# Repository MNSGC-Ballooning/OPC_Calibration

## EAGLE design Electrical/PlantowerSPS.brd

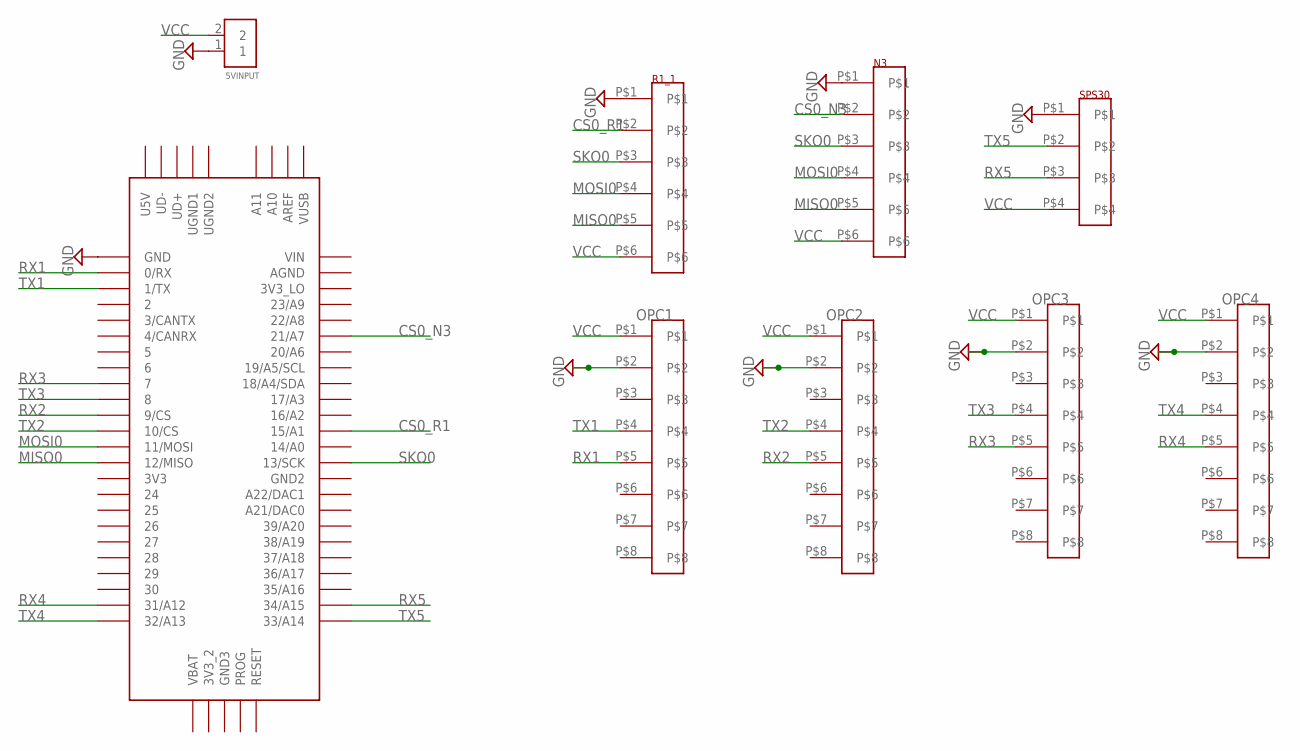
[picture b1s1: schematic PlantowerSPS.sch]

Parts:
5VINPUT: 2PIN_TERMINAL_BLOCK
N3: 6PINHEADER
OPC1, OPC2, OPC3, OPC4: 8PINHEADER
R1_1: 6PINHEADER
SPS30: 4PINHEADER
U$1: TEENSY_3.5/3.6

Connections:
CS0_N3: N3.P$2, U$1.21/A7
CS0_R1: R1_1.P$2, U$1.15/A1
GND: 5VINPUT.1, N3.P$1, OPC1.P$2, OPC2.P$2, OPC3.P$2, OPC4.P$2, R1_1.P$1, SPS30.P$1, U$1.GND
MISO0: N3.P$5, R1_1.P$5, U$1.12/MISO
MOSI0: N3.P$4, R1_1.P$4, U$1.11/MOSI
RX1: OPC1.P$5, U$1.0/RX
RX2: OPC2.P$5, U$1.9/CS
RX3: OPC3.P$5, U$1.7
RX4: OPC4.P$5, U$1.31/A12
RX5: SPS30.P$3, U$1.34/A15
SKO0: N3.P$3, R1_1.P$3, U$1.13/SCK
TX1: OPC1.P$4, U$1.1/TX
TX2: OPC2.P$4, U$1.10/CS
TX3: OPC3.P$4, U$1.8
TX4: OPC4.P$4, U$1.32/A13
TX5: SPS30.P$2, U$1.33/A14
VCC: 5VINPUT.2, N3.P$6, OPC1.P$1, OPC2.P$1, OPC3.P$1, OPC4.P$1, R1_1.P$6, SPS30.P$4

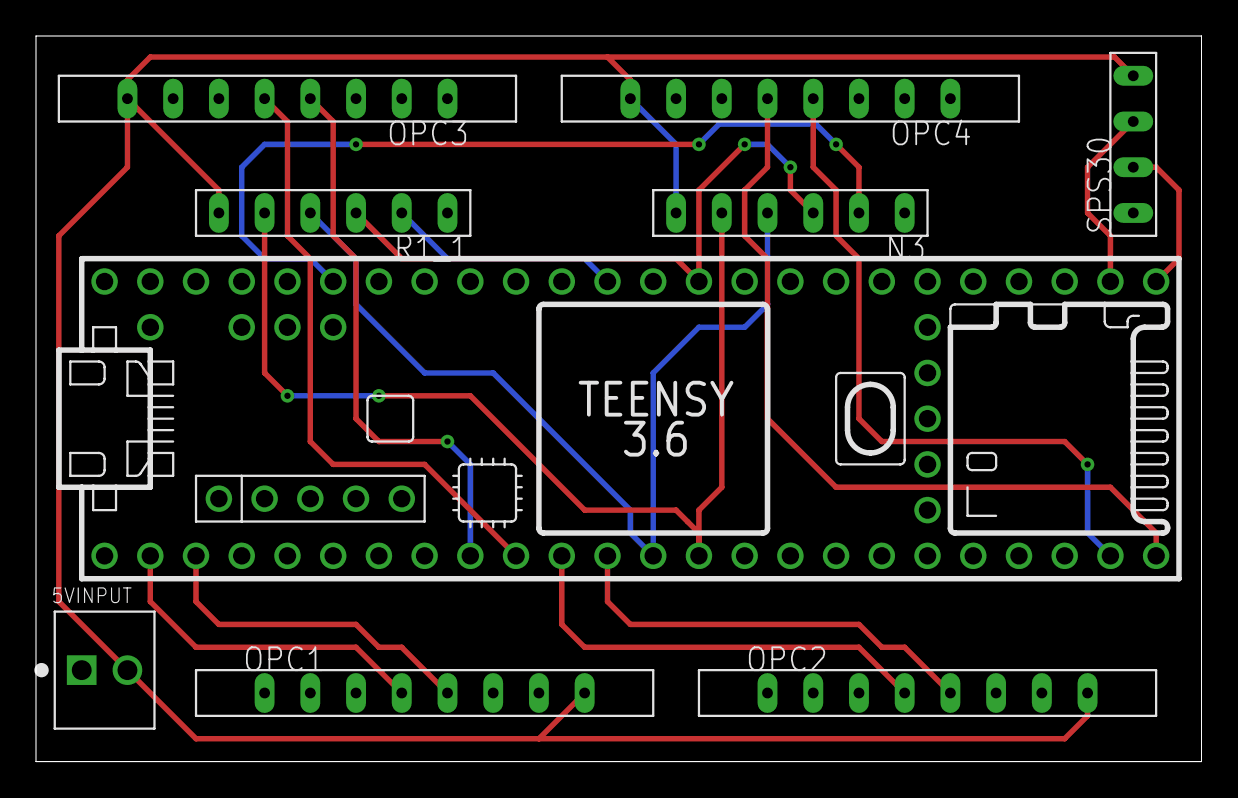
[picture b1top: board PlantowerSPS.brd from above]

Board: 2 copper layers, 64.8 x 40.3 mm, 9 parts (0 on the bottom side), 17 nets.

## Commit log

2020-01-14 Arduino script for the Plantower
2020-01-16 added the pcb schematic and fixed logging for code
2020-01-16 Fixed logging issue
2020-01-21 First Plantower Calibration test
